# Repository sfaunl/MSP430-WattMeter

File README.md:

# About
2 channel Wattmeter using MSP430

# Renders

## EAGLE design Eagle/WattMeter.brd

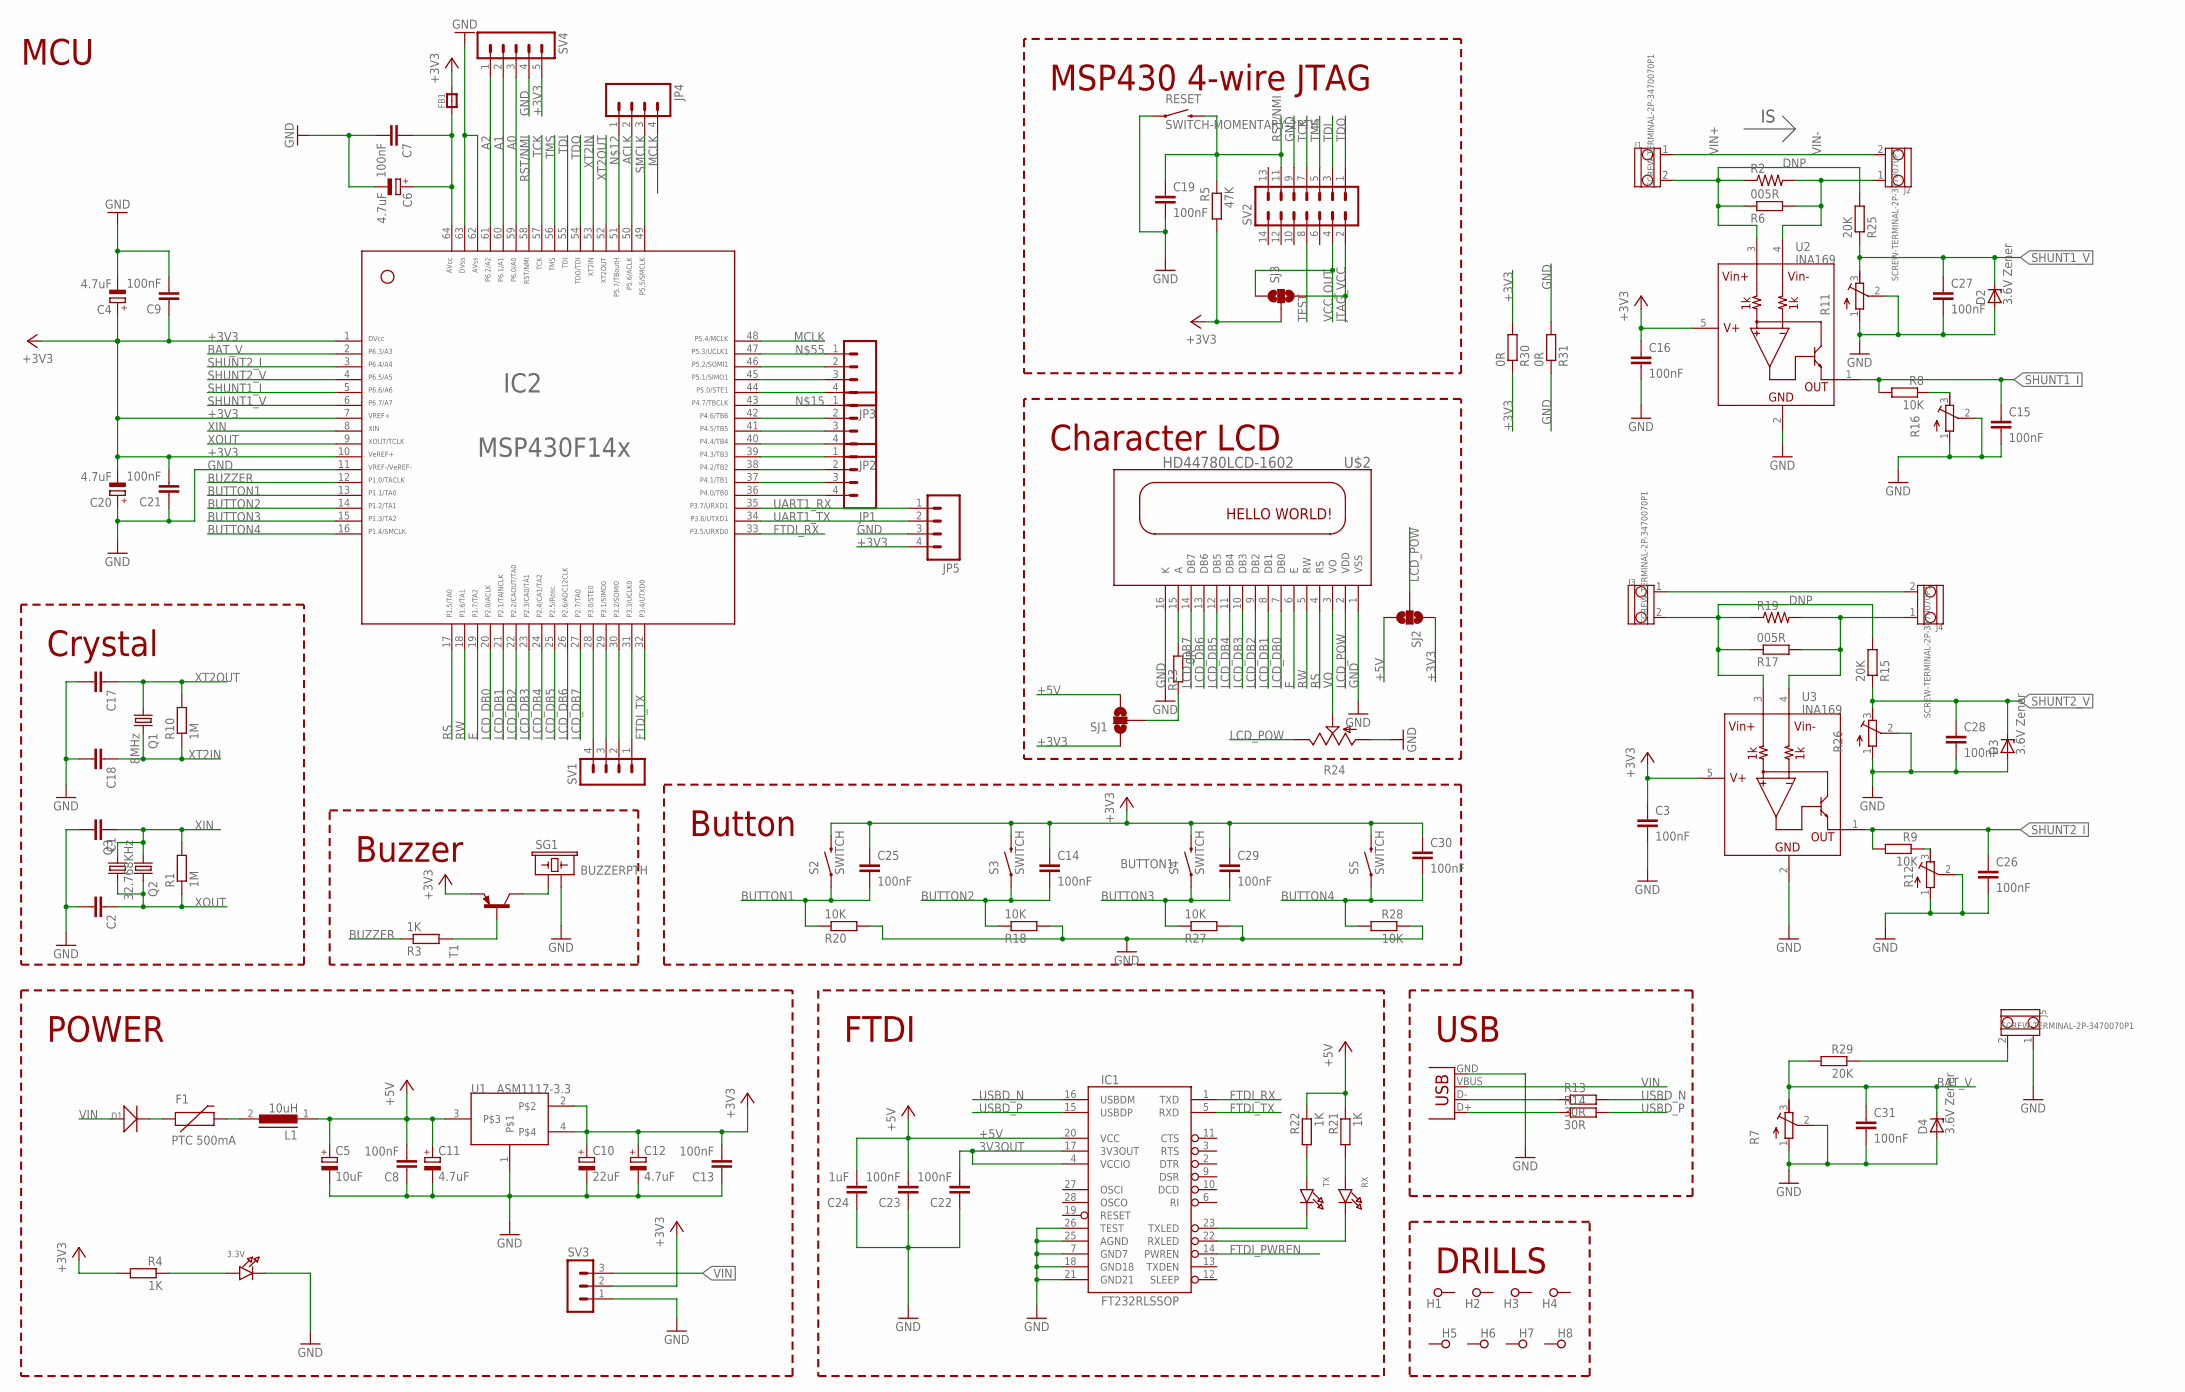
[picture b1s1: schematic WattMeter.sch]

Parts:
3.3V: LED0805; CHIPLED_0805
C1, C2, C17, C18: C-EUC0805; C0805
C3, C7, C8, C9, C13, C14, C15, C16, C19, C21, C22, C23, C25, C26, C27, C28, C29, C30, C31: 100nF; C0805
C4, C6, C11, C12, C20: 4.7uF; A/3216-18W
C5: 10uF; 150CLZ-0810
C10: 22uF; B/3528-21R
C24: 1uF; C0805
D1: D-D1206; LL-34
D2, D3, D4: 3.6V Zener; SMB
F1: PTC 500mA; PTC-1206
FB1: FERRITE0805; 0805
H1, H2, H3, H4, H5, H6, H7, H8: SPECIAL_DRILL_0.1000; PAD_0.1000
IC1: FT232RLSSOP; SSOP28DB
IC2: F14X---PM/PAG64; PM/PAG64
J1, J2, J3, J4, J5: SCREW-TERMINAL-2P-3470070P1; 2P-3.5
JP1, JP2, JP3, JP4, JP5: M041.27MM; 1X04-1.27MM
L1: 10uH; DR74
Q1: 8MHz; HC49U-V
Q2: 32.768KHz; HC49U-V
Q3: CRYSTALTC38H; TC38H
R1, R10: 1M; R0805
R2, R19: RESISTORPTH-2W; AXIAL-0.8
R3, R4, R21, R22: 1K; R0805
R5: 47K; R0805
R6, R17: 005R; R2512
R7, R11, R12, R16, R26: R-TRIMM3296W; RTRIM3296W
R8, R9, R18, R20, R27, R28: 10K; R0805
R13, R14: 30R; R0805
R15, R25, R29: 20K; R0805
R23: 0R; R0805
R24: TRIM_US-3223G; 3223G
R30, R31: 0R; R1206
RESET: SWITCH-MOMENTARY-2PTH; TACTILE-PTH
RX: LED0805; CHIPLED_0805
S2, S3, S4, S5: SWITCH; TACTILE-PTH
SG1: BUZZERPTH; BUZZER-12MM
SJ1, SJ2, SJ3: SOLDERJUMPER_2WAYS; SJ_3
SV1: MA04-1
SV2: ML14L
SV3: MA03-1
SV4: MA05-1
T1: MMBT3906LT1-PNP-SOT23-BEC; SOT23-BEC
TX: LED0805; CHIPLED_0805
U1: ASM1117-3.3; SOT223
U2, U3: INA169; SOT23-5
U$2: HD44780LCD-1602; LCD1602
X2: USBPTH; USB-B-PTH

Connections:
3V3OUT: C22.2, IC1.4 (VCCIO), IC1.17 (3V3OUT)
+3V3: C3.1, C4.+, C9.1, C10.+, C12.+, C13.2, C14.1, C16.1, C20.-, C21.2, C25.1, C29.1, C30.1, FB1.1, IC2.1, IC2.7, IC2.10, JP5.4, R4.2, R5.2, R30.1, R30.2, S2.3 (2), S3.3 (2), S4.3 (2), S5.3 (2), SJ1.1, SJ2.1, SJ3.2, SV3.2, SV4.5, T1.E, U1.2, U1.4, U2.5 (V+), U3.5 (V+)
+5V: C5.+, C8.2, C11.+, C23.2, C24.2, IC1.20 (VCC), L1.1, R21.1, R22.1, SJ1.3, SJ2.3, U1.3
A0: IC2.59, SV4.3
A1: IC2.60, SV4.2
A2: IC2.61, SV4.1
ACLK: IC2.50, JP4.2
BAT_V: C31.1, D4.C, IC2.2, R7.3 (E), R29.2
BUTTON1: C25.2, IC2.13, R20.1, S2.1
BUTTON2: C14.2, IC2.14, R18.1, S3.1
BUTTON3: C29.2, IC2.15, R27.1, S4.1
BUTTON4: C30.2, IC2.16, R28.2, S5.1
BUZZER: IC2.12, R3.1
E: IC2.19, U$2.6 (E)
FTDI_PWREN: IC1.14 (PWREN)
FTDI_RX: IC1.1 (TXD), IC2.33
FTDI_TX: IC1.5 (RXD), IC2.32
GND: 3.3V.C, C1.2, C2.2, C3.2, C4.-, C5.-, C6.-, C7.2, C8.1, C9.2, C10.-, C11.-, C12.-, C13.1, C15.2, C16.2, C17.2, C18.2, C19.2, C20.+, C21.1, C22.1, C23.1, C24.1, C26.2, C27.2, C28.2, C31.2, D2.A, D3.A, D4.A, IC1.7 (GND7), IC1.18 (GND18), IC1.21 (GND21), IC1.25 (AGND), IC1.26 (TEST), IC2.11, IC2.62, IC2.63, J5.1, JP5.3, R7.1 (A), R7.2 (S), R11.1 (A), R11.2 (S), R12.1 (A), R12.2 (S), R16.1 (A), R16.2 (S), R18.2, R20.2, R24.1 (A), R26.1 (A), R26.2 (S), R27.2, R28.1, R31.1, R31.2, RESET.1, SG1.- (2), SV2.9, SV3.1, SV4.4, U1.1, U2.2 (GND), U3.2 (GND), U$2.1 (VSS), U$2.16 (K), X2.GND
JTAG_VCC: SJ3.3, SV2.2
LCD_DB0: IC2.20, U$2.7 (DB0)
LCD_DB1: IC2.21, U$2.8 (DB1)
LCD_DB2: IC2.22, U$2.9 (DB2)
LCD_DB3: IC2.23, U$2.10 (DB3)
LCD_DB4: IC2.24, U$2.11 (DB4)
LCD_DB5: IC2.25, U$2.12 (DB5)
LCD_DB6: IC2.26, U$2.13 (DB6)
LCD_DB7: IC2.27, U$2.14 (DB7)
LCD_POW: R24.3 (E), SJ2.2, U$2.2 (VDD)
MCLK: IC2.48, JP4.4
unnamed: SG1.+ (1), T1.C
unnamed: D1.C (-), F1.1
unnamed: C6.+, C7.1, FB1.2, IC2.64
unnamed: IC2.29, SV1.3
unnamed: F1.2, L1.2
unnamed: IC2.38, JP1.2
unnamed: 3.3V.A, R4.1
unnamed: IC2.37, JP1.3
unnamed: IC2.28, SV1.4
unnamed: R8.1, R16.3 (E)
unnamed: J1.1, J2.2
unnamed: IC2.51, JP4.1
unnamed: J5.2, R29.1
unnamed: R3.2, T1.B
unnamed: IC2.43, JP2.1
unnamed: IC2.36, JP1.4
unnamed: R9.1, R12.3 (E)
unnamed: J3.1, J4.2
unnamed: R23.2, SJ1.2
unnamed: R23.1, U$2.15 (A)
unnamed: R22.2, TX.A
unnamed: IC1.23 (TXLED), TX.C
unnamed: R21.2, RX.A
unnamed: IC2.46, JP3.2
unnamed: IC2.44, JP3.4
unnamed: IC1.22 (RXLED), RX.C
unnamed: IC2.42, JP2.2
unnamed: IC2.40, JP2.4
unnamed: IC2.39, JP1.1
unnamed: IC2.41, JP2.3
unnamed: IC2.45, JP3.3
unnamed: IC2.47, JP3.1
unnamed: IC2.30, SV1.2
unnamed: IC2.31, SV1.1
unnamed: R13.1, X2.D-
unnamed: R14.1, X2.D+
unnamed: J4.1, R17.2, R19.P$2 (2), U3.4 (VIN-)
unnamed: J3.2, R15.2, R17.1, R19.P$1 (1), U3.3 (VIN+)
RS: IC2.17, U$2.4 (RS)
RST/NMI: C19.1, IC2.58, R5.1, RESET.3 (2), SV2.11
RW: IC2.18, U$2.5 (RW)
SHUNT1_I: C15.1, IC2.5, R8.2, U2.1 (OUT)
SHUNT1_V: C27.1, D2.C, IC2.6, R11.3 (E), R25.1
SHUNT2_I: C26.1, IC2.3, R9.2, U3.1 (OUT)
SHUNT2_V: C28.1, D3.C, IC2.4, R15.1, R26.3 (E)
SMCLK: IC2.49, JP4.3
TCK: IC2.57, SV2.7
TDI: IC2.55, SV2.3
TDO: IC2.54, SV2.1
TEST: SV2.8
TMS: IC2.56, SV2.5
UART1_RX: IC2.35, JP5.1
UART1_TX: IC2.34, JP5.2
USBD_N: IC1.16 (USBDM), R13.2
USBD_P: IC1.15 (USBDP), R14.2
VCC_OUT: SJ3.1, SV2.4
VIN: D1.A (+), SV3.3, X2.VBUS
VIN+: J1.2, R2.P$1 (1), R6.1, R25.2, U2.3 (VIN+)
VIN-: J2.1, R2.P$2 (2), R6.2, U2.4 (VIN-)
VO: R24.2 (S), U$2.3 (VO)
XIN: C1.1, IC2.8, Q2.1, Q3.2, R1.2
XOUT: C2.1, IC2.9, Q2.2, Q3.1, R1.1
XT2IN: C18.1, IC2.53, Q1.2, R10.1
XT2OUT: C17.1, IC2.52, Q1.1, R10.2

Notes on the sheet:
MSP430 4-wire JTAG
POWER
USB
Character LCD
FTDI
DRILLS
Button
Crystal
Buzzer
MCU

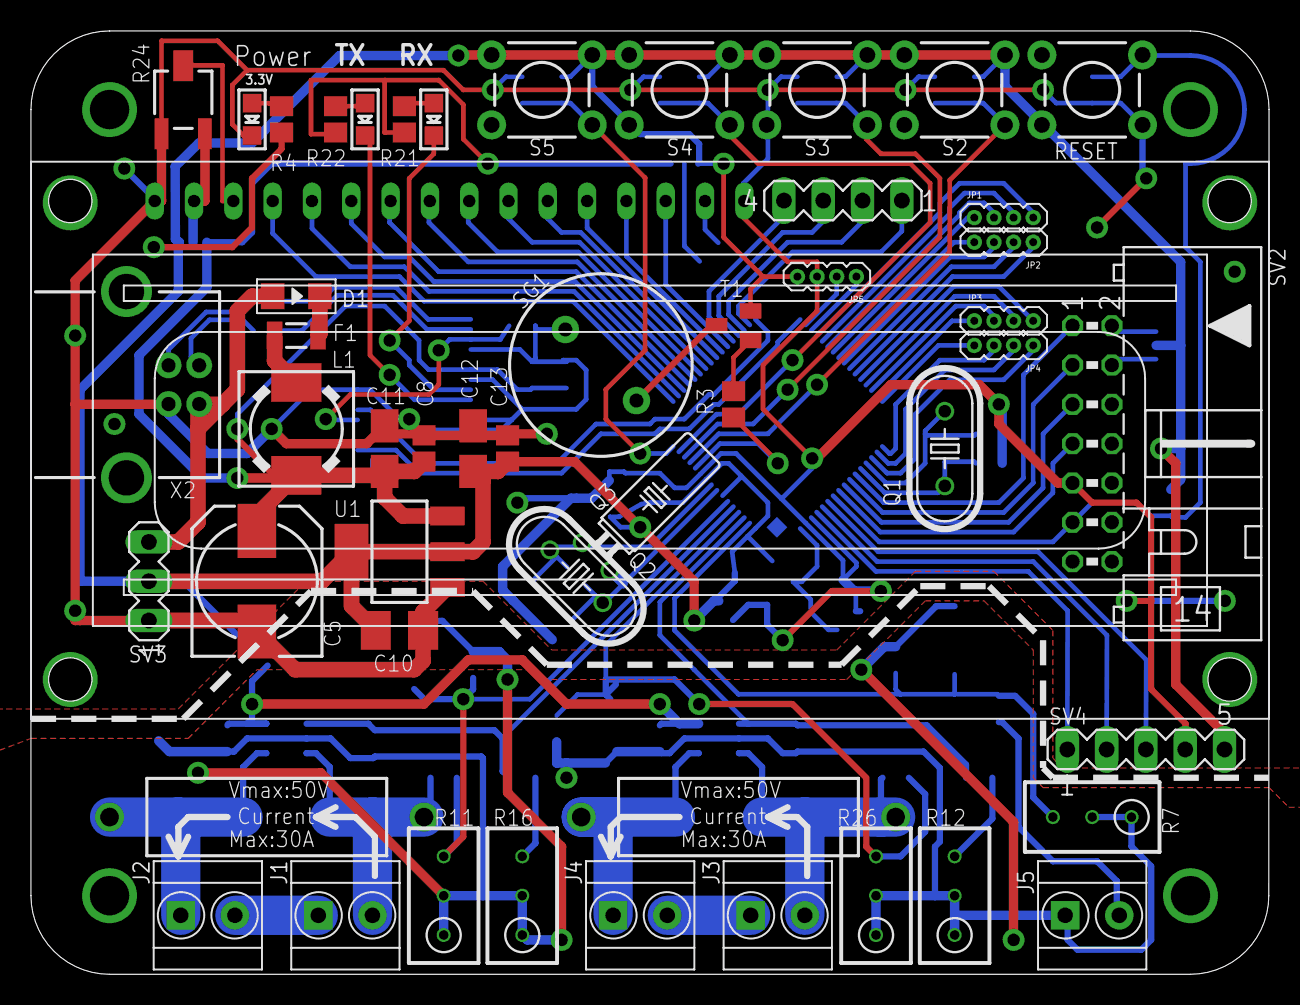
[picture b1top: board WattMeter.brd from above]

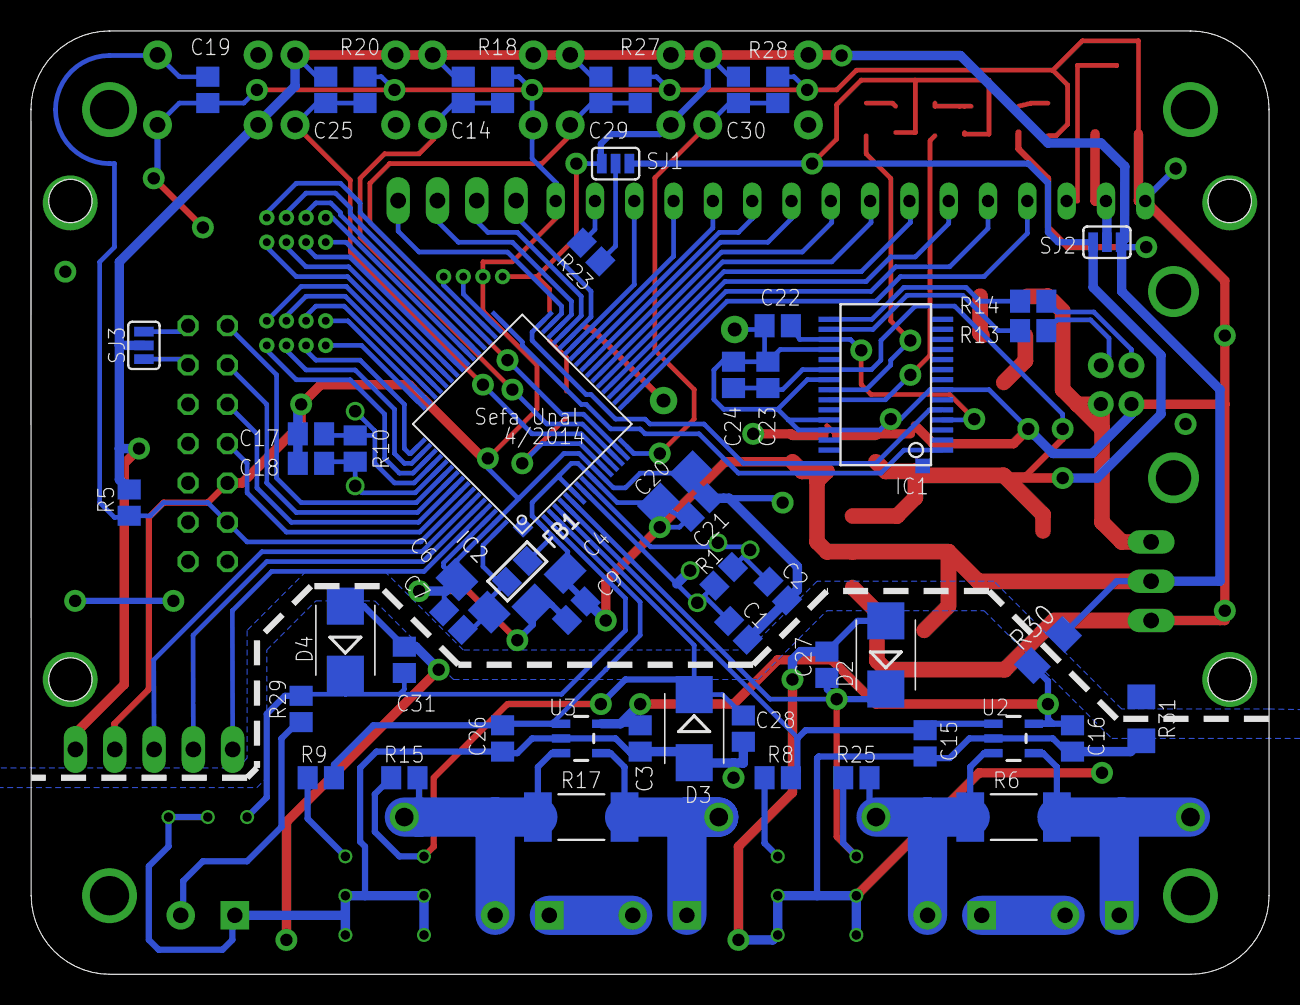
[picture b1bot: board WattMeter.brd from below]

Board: 4 copper layers, 80.0 x 61.0 mm, 114 parts (55 on the bottom side), 91 nets.

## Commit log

2014-12-11 First version.
2023-01-12 remove unnecessary files
2023-01-12 change license to mit
2023-01-12 add render images to readme

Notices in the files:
parts and their libraries:
microbuilder: This work is placed in the public domain, and may be freely used for commercial and non-commercial work with the following conditions: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
SparkFun-AnalogIC: Licensing: CC v3.0 Share-Alike You are welcome to use this library for commercial purposes.
